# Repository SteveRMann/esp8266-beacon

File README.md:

# esp8266-beacon
This is a simple PCB that combines an ESP8266-01 and a buck voltage converter set for 3.3V.
The ESPHome code simply connects to the local WiFi when in range.
The project came about because I connected my garage door opener to Alexa and I wanted to not let the doors open if the associated vehicle was not in WiFi range.

In Home Assistant:
I have an ESP01 in my Jeep that I use for presence.
If the ESP connects, then the Jeep is present.
I use a binary helper that I turn on on the dashboard that is basically a semaphore to tell the ESP that I want it to not go to sleep. The test_ota script in the code below is where this is tested when the ESP boots.

The sequence is:
1. Turn on OTA mode.
2. Wait for the sleep period to end, then the ESP reboots and will not go to sleep.
3. Perform my OTA upload.
4. Turn off the OTA mode.
5. Press "Restart" on the dashboard to reboot the ESP.

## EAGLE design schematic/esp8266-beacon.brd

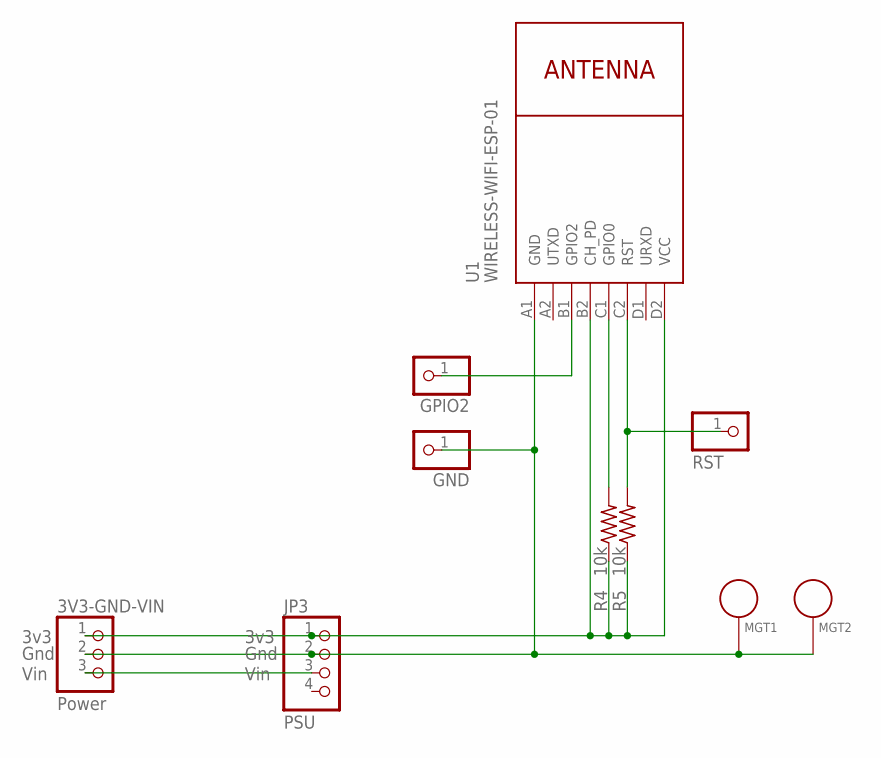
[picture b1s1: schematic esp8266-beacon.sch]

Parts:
3V3-GND-VIN: Power; 1X03
GND: RST; 1X01
GPIO2: RST; 1X01
JP3: PSU; 1X04
MGT1, MGT2: BEAGLEBONEBLACK_MOUNTING_HOLE
R4, R5: 10k; 0207/10
RST: RST; 1X01
U1: WIRELESS-WIFI-ESP-01

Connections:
3V3: 3V3-GND-VIN.1, JP3.1, R4.1, R5.1, U1.B2 (CH_PD), U1.D2 (VCC)
GND: 3V3-GND-VIN.2, GND.1, JP3.2, MGT1.P$1, MGT2.P$1, U1.A1 (GND)
unnamed: GPIO2.1, U1.B1 (GPIO2)
unnamed: 3V3-GND-VIN.3, JP3.3
unnamed: R4.2, U1.C1 (GPIO0)
unnamed: R5.2, RST.1, U1.C2 (RST)

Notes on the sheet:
Gnd
Vin
3v3

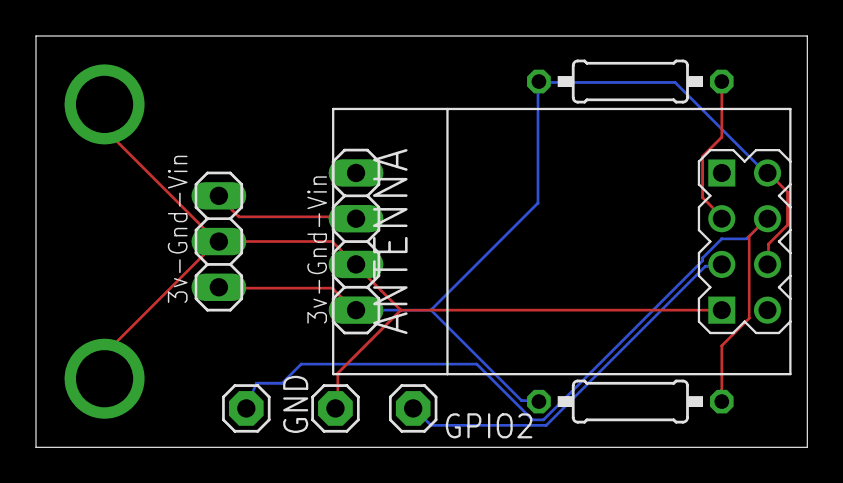
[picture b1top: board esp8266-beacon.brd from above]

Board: 2 copper layers, 42.9 x 22.9 mm, 10 parts (0 on the bottom side), 6 nets.

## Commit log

2022-03-18 Create placeholder
2022-03-26 Updates YAML code
2022-03-26 Changed name from jeep to esp8266
2022-03-26 Fixed the gitignore file
2023-01-16 Update jeep.yaml
    Updated to test for OTA switch on the dashboard

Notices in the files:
parts and their libraries:
diy-modules: Released under the Creative Commons Attribution 4.0 International License: http://creativecommons.org/licenses/by/4.0
